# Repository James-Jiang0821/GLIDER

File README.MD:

# Glider System

Top-level repo for the underwater glider. 

ROS 2 stack on the Raspberry Pi, Teensy firmware for the P&R and VBD boards, KiCad designs for the custom electronics, and post-test analysis tooling.

Each subfolder has its own README with full details.

## Subsystems

- **[ROS2_SYSTEM/](ROS2_SYSTEM/README.md)** — ROS 2 Jazzy stack on the Raspberry Pi: sensor drivers, mission state machine, inner/outer-loop controller, safety watchdog, Iridium telemetry, and the CAN bridge to the Teensy boards.
- **[TEENSY/](TEENSY/)** — Teensy 4.0 firmware for the actuator boards.
  - **[tsyPR/](TEENSY/tsyPR/README.md)** — Pitch & Roll firmware (stepper-driven pitch mass + roll mass).
  - **[tsyVBDL/](TEENSY/tsyVBDL/README.md)** — Variable Buoyancy Device firmware (lead-screw piston with closed-loop position control).
- **[PCB/](PCB/README.MD)** — KiCad schematics and layouts for the custom P&R and VBD boards.
- **[BATTERY_BOARD/](BATTERY_BOARD/README.MD)** — KiCad designs for the P&R and VBD battery boards (A/B variants).
- **[ROS2_TESTING/](ROS2_TESTING/README.md)** — Post-test analysis scripts for ROS 2 bag files (`.mcap` to CSV).

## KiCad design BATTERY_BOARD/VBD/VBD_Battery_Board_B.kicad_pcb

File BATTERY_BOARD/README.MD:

# Battery Board

KiCad design files for the glider's battery boards.

## Subsystems

- **P&R/** — Pitch & Roll battery board. Powers the P&R subsystem; A and B variants.
- **VBD/** — Variable Buoyancy Device battery board. Powers the VBD subsystem; A and B variants.

Each folder contains the KiCad schematic (`.kicad_sch`), PCB layout (`.kicad_pcb`), and project file (`.kicad_pro`) for both A and B revisions.

## Authors

Bartol Vahcic

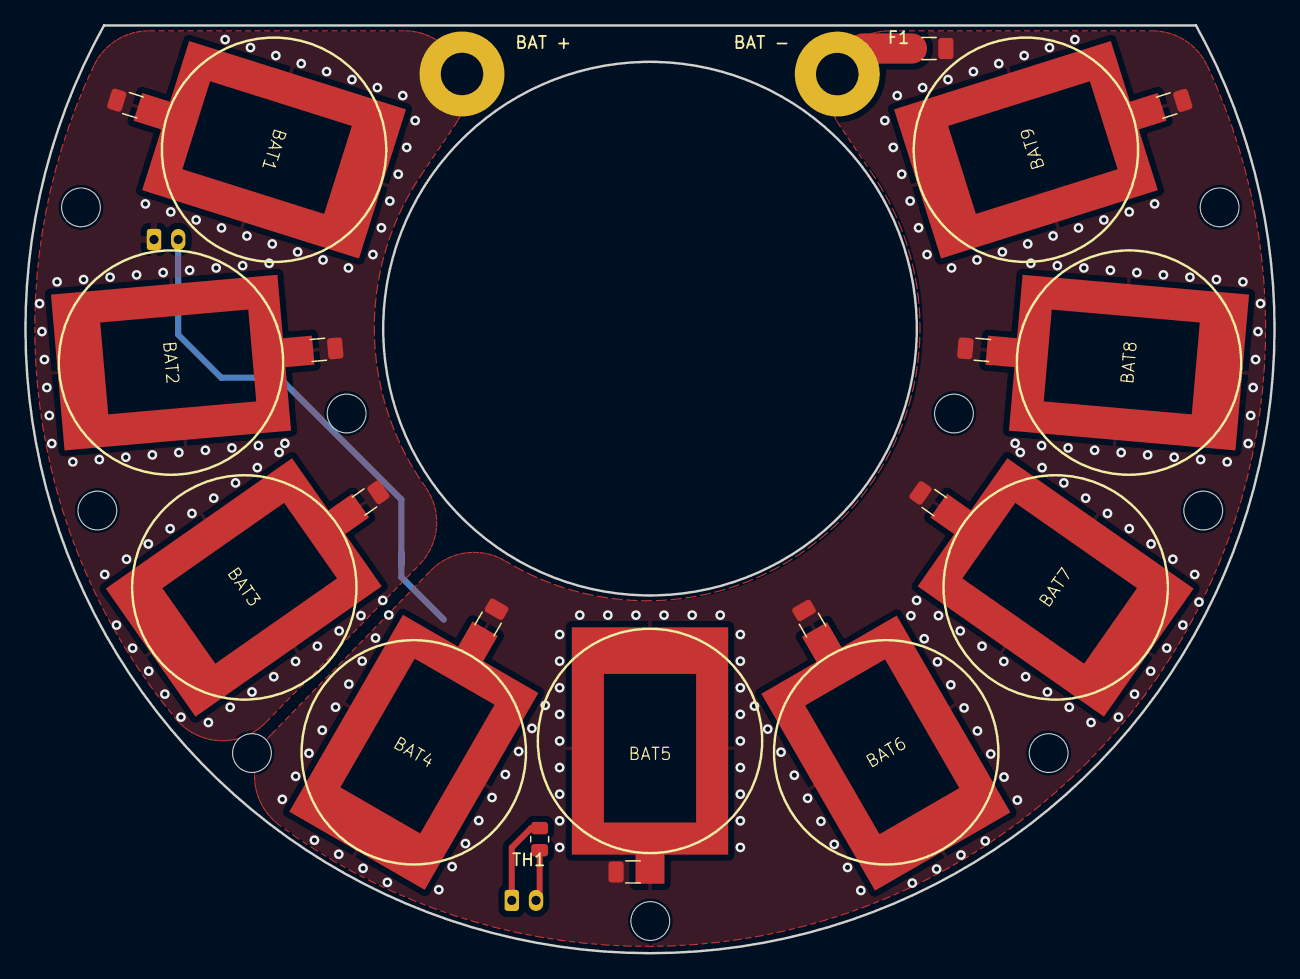
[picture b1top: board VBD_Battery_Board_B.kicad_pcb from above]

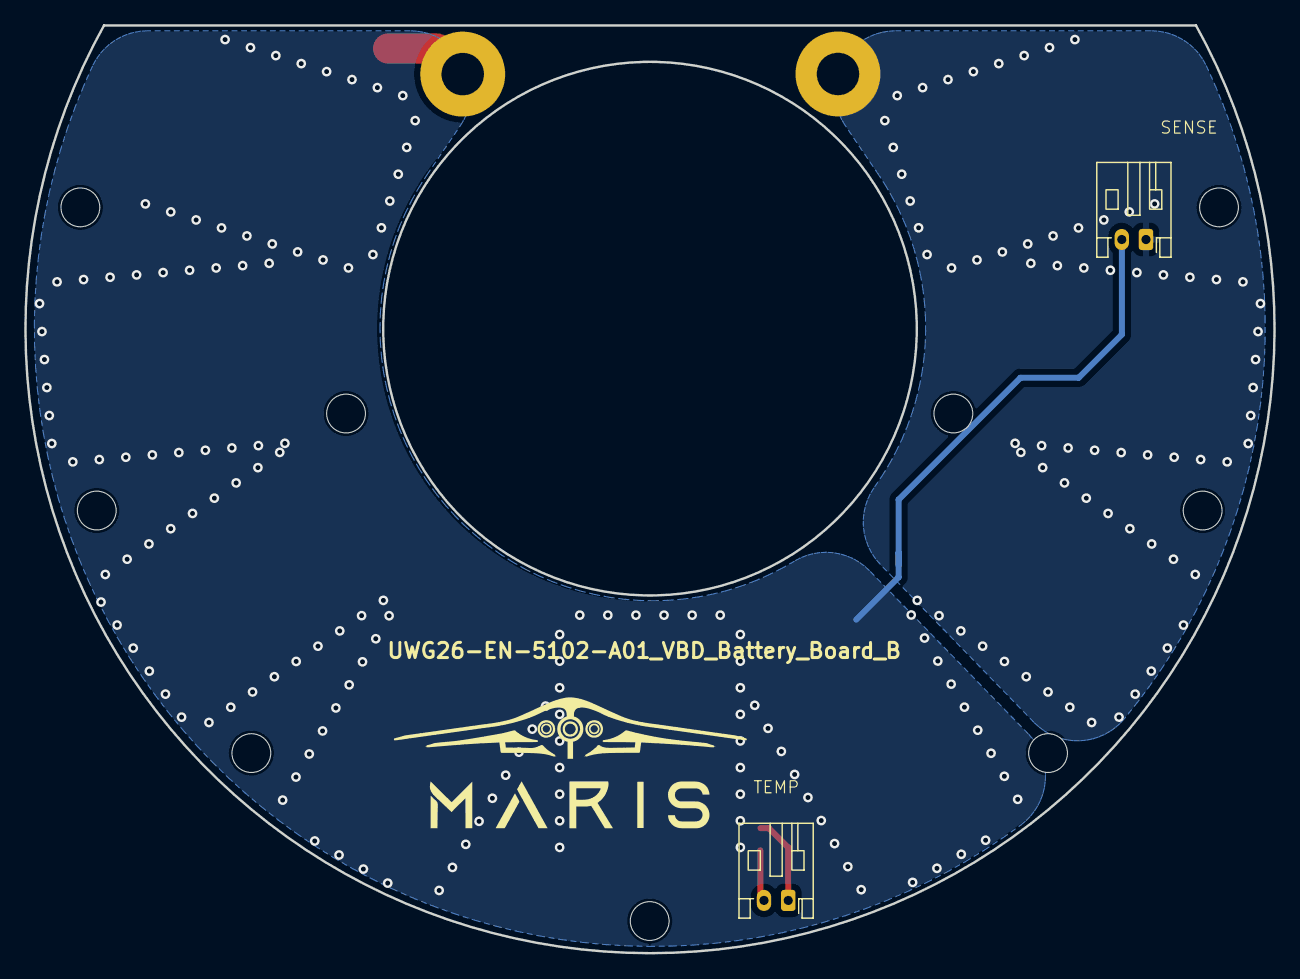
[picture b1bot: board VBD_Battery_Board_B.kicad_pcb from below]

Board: 2 copper layers, 103.0 x 76.5 mm, 15 parts (2 on the bottom side), 5 nets.

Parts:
BAT1, BAT2, BAT3, BAT4, BAT5, BAT6, BAT7, BAT8, BAT9: Keystone_109-2
BAT +: Conn_01x01_Pin; MountingHole_3.5mm_Pad
BAT -: Conn_01x01_Pin; MountingHole_3.5mm_Pad
F1: Fuse; Fuse_1206_3216Metric
J1, J4: Conn_01x02_Pin; JST_PH_S2B-PH-K_1x02_P2.00mm_Horizontal
TH1: Thermistor_NTC; R_0805_2012Metric

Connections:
/S1_POS: BAT1.1, BAT2.1, BAT3.1, BAT +.1, J1.1
/S3_POS: BAT4.1, BAT5.1, BAT6.1, BAT7.1, BAT8.1, BAT9.1, F1.2, J1.2
/TEMP: J4.1, TH1.1
/TEMP_GND: J4.2, TH1.2
unnamed: BAT -.1, F1.1

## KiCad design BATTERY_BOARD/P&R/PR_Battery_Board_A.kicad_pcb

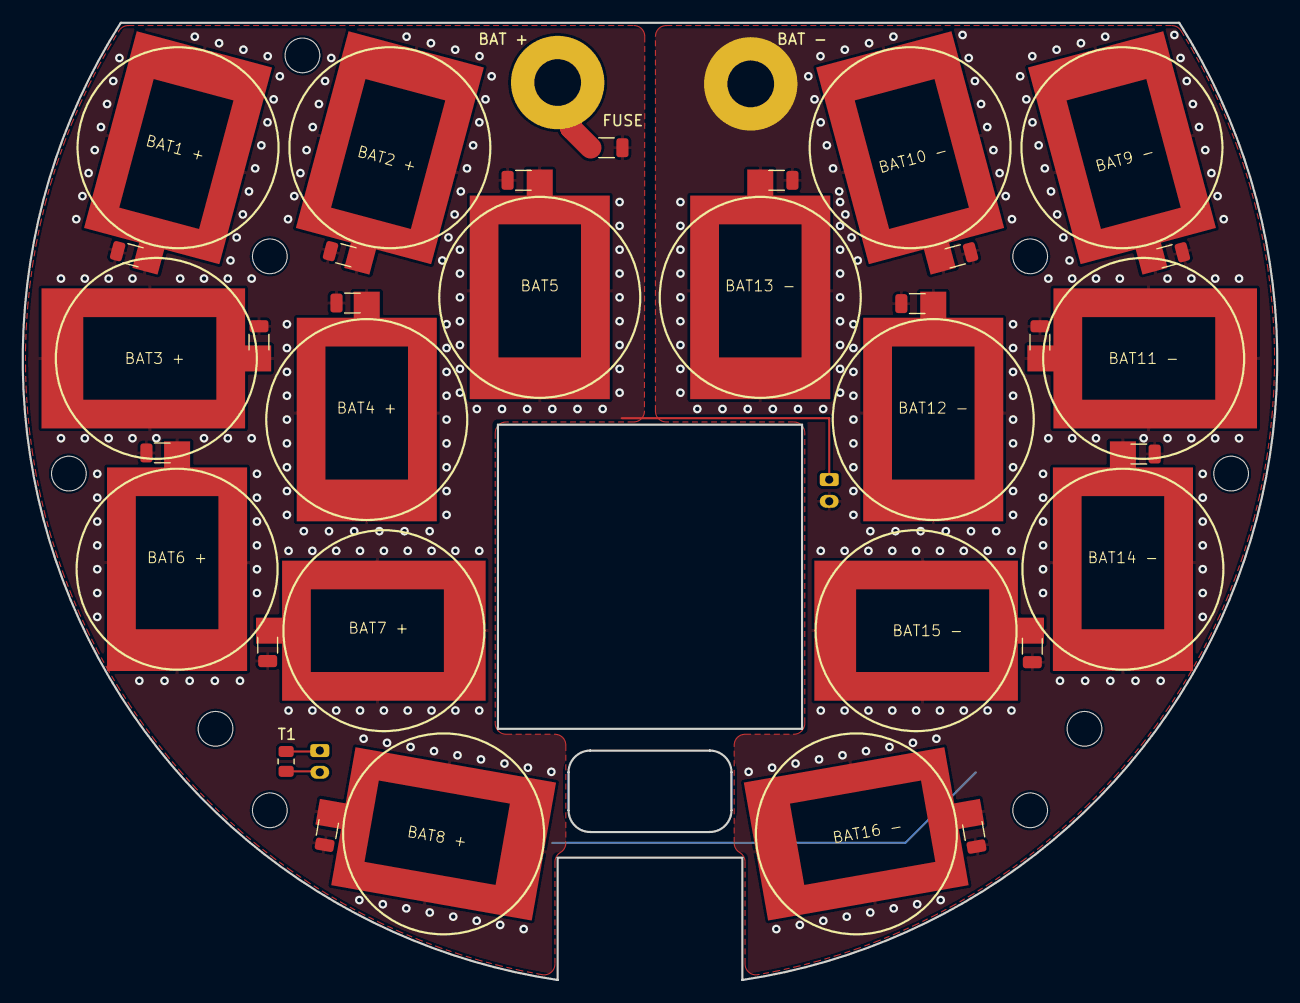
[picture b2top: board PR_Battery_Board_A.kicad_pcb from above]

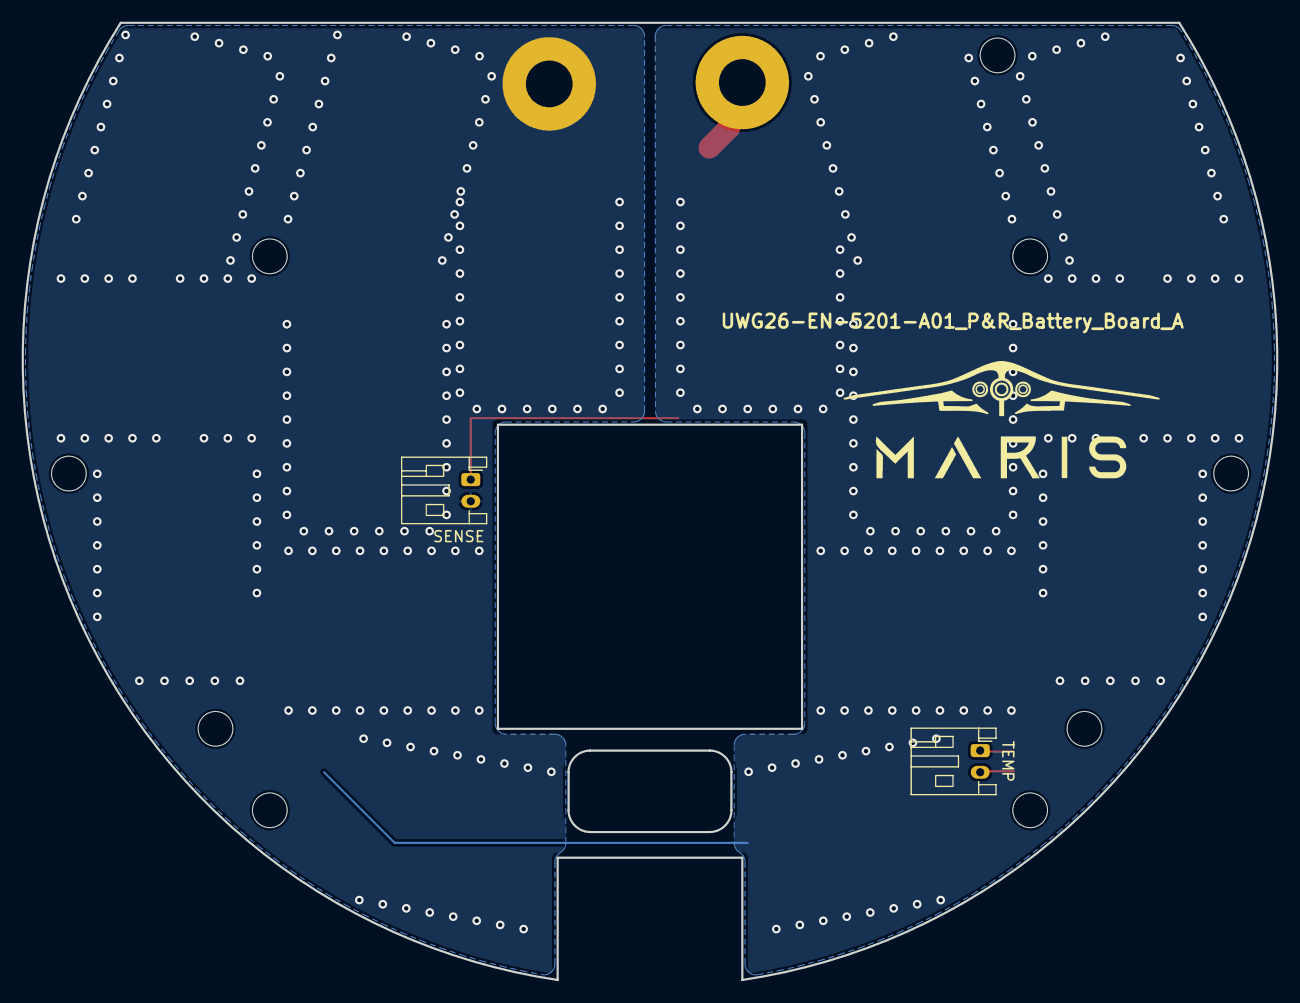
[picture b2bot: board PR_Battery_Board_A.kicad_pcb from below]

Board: 2 copper layers, 115.5 x 88.1 mm, 38 parts (2 on the bottom side), 5 nets.

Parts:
BAT1 +, BAT2 +, BAT3 +, BAT4 +, BAT5, BAT6 +, BAT7 +, BAT8 +, BAT9 -, BAT10 -, BAT11 -, BAT12 -, BAT13 -, BAT14 -, BAT15 -, BAT16 -: Keystone_109-2
BAT +: MountingHole_Pad; MountingHole_4.3mm_M4_Pad
BAT -: MountingHole_Pad; MountingHole_4.3mm_M4_Pad
F1, F2, F3, F4, F5, F6, F7, F8, F9, F10, F11, F12, F13, F14, F15, F16: DNP; R_1206_3216Metric
FUSE: F10; R_1206_3216Metric
SENSE: Conn_01x02_Pin; JST_PH_S2B-PH-K_1x02_P2.00mm_Horizontal
T1: 10K NTC; R_0805_2012Metric
TEMP: Conn_01x02_Pin; JST_PH_S2B-PH-K_1x02_P2.00mm_Horizontal

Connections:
/B_PLUS: BAT +.1, FUSE.2
/NTC_GND: T1.1, TEMP.2
/NTC_SIG: T1.2, TEMP.1
/S1_POS: BAT1 +.1, BAT2 +.1, BAT3 +.1, BAT4 +.1, BAT5.1, BAT6 +.1, BAT7 +.1, BAT8 +.1, F1.1, F1.2, F2.1, F2.2, F3.1, F3.2, F4.1, F4.2, F5.1, F5.2, F6.1, F6.2, F7.1, F7.2, F8.1, F8.2, FUSE.1, SENSE.1
/S2_NEG: BAT9 -.1, BAT10 -.1, BAT11 -.1, BAT12 -.1, BAT13 -.1, BAT14 -.1, BAT15 -.1, BAT16 -.1, BAT -.1, F9.1, F9.2, F10.1, F10.2, F11.1, F11.2, F12.1, F12.2, F13.1, F13.2, F14.1, F14.2, F15.1, F15.2, F16.1, F16.2, SENSE.2

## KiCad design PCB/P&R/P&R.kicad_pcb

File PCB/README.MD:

# PCB

KiCad design files for the glider's custom boards.

## Subsystems

- **P&R/** — Pitch & Roll board. Drives the pitch and roll actuators; also connects to the Raspberry Pi.
- **VBD/** — Variable Buoyancy Device board. Drives the VBD pump/valve subsystem.

Each folder contains the KiCad schematic (`.kicad_sch`) and PCB layout (`.kicad_pcb`); `P&R/` also includes the project file (`.kicad_pro`).

## Authors

Qihao Zhang

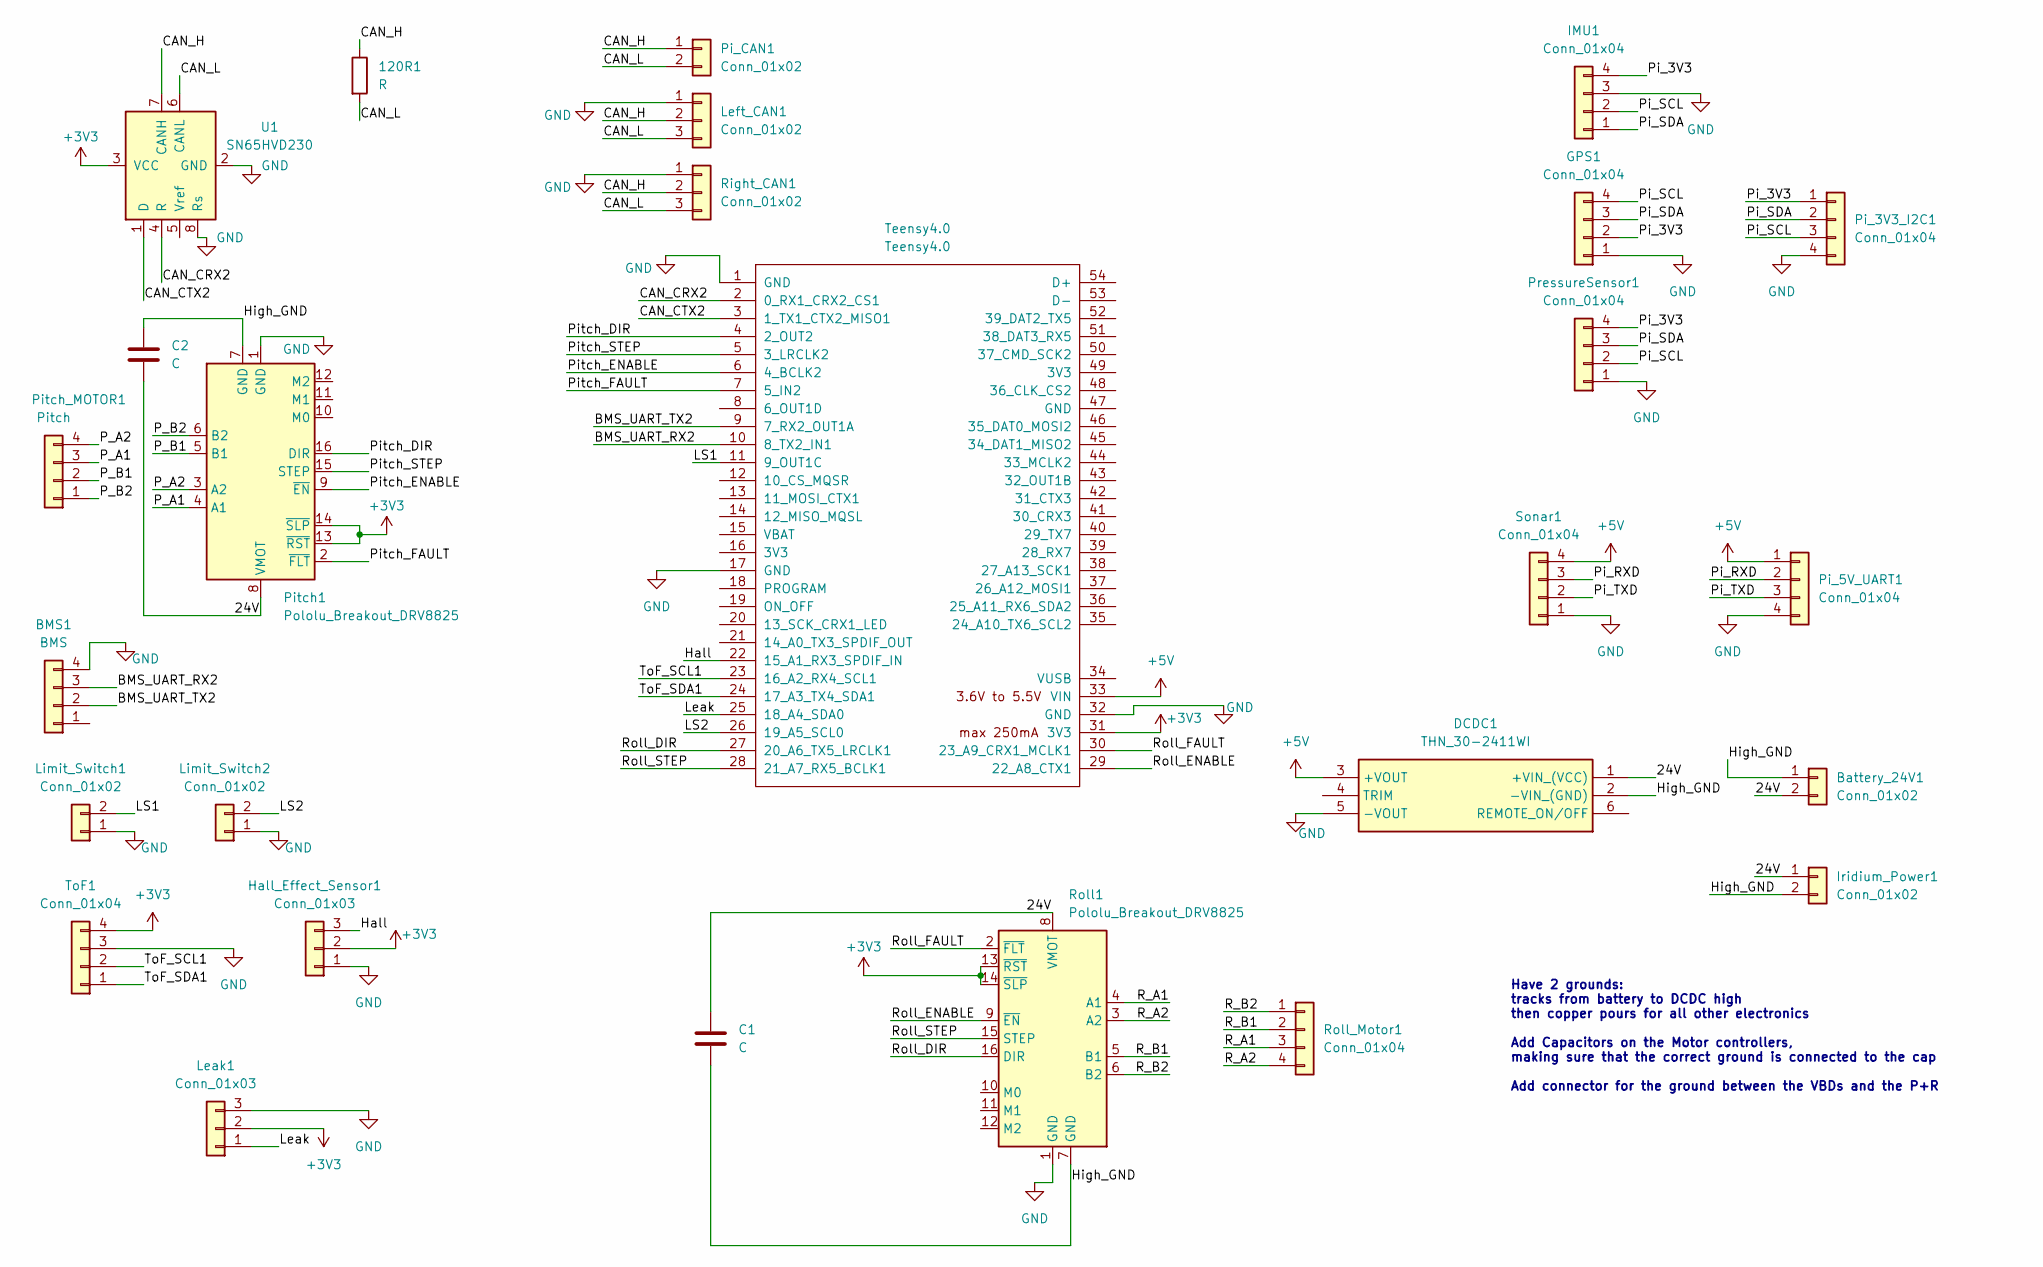
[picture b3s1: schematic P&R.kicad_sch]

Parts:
120R1: R; R_0805_2012Metric_Pad1.20x1.40mm_HandSolder
BMS1: BMS; JST_XH_B4B-XH-A_1x04_P2.50mm_Vertical
Battery_24V1: Conn_01x02; TerminalBlock_WAGO_2601-1102_1x02_P3.50mm_Horizontal
C1, C2: C; CP_Radial_D8.0mm_P3.50mm
DCDC1: THN_30-2411WI; THN302415WI; Mouser Part Number 495-THN-30-2411WI
GPS1: Conn_01x04; NewnewGNSS
Hall_Effect_Sensor1: Conn_01x03; JST_XH_B3B-XH-A_1x03_P2.50mm_Vertical
IMU1: Conn_01x04; JST_XH_B4B-XH-A_1x04_P2.50mm_Vertical
Iridium_Power1: Conn_01x02; JST_XH_B2B-XH-A_1x02_P2.50mm_Vertical
Leak1: Conn_01x03; SOS_Leak_Sensor_Board
Left_CAN1: Conn_01x02; JST_XH_B3B-XH-A_1x03_P2.50mm_Vertical
Limit_Switch1, Limit_Switch2: Conn_01x02; JST_XH_B2B-XH-A_1x02_P2.50mm_Vertical
Pi_3V3_I2C1, Pi_5V_UART1: Conn_01x04; JST_XH_B4B-XH-A_1x04_P2.50mm_Vertical
Pi_CAN1: Conn_01x02; JST_XH_B2B-XH-A_1x02_P2.50mm_Vertical
Pitch1: Pololu_Breakout_DRV8825; Pololu_Breakout-16_15.2x20.3mm
Pitch_MOTOR1: Pitch; JST_XH_B4B-XH-A_1x04_P2.50mm_Vertical
PressureSensor1: Conn_01x04; JST_XH_B4B-XH-A_1x04_P2.50mm_Vertical
Right_CAN1: Conn_01x02; JST_XH_B3B-XH-A_1x03_P2.50mm_Vertical
Roll1: Pololu_Breakout_DRV8825; Pololu_Breakout-16_15.2x20.3mm
Roll_Motor1: Conn_01x04; JST_XH_B4B-XH-A_1x04_P2.50mm_Vertical
Sonar1: Conn_01x04; JST_XH_B4B-XH-A_1x04_P2.50mm_Vertical
Teensy4.0: Teensy4.0; Teensy40
ToF1: Conn_01x04; JST_XH_B4B-XH-A_1x04_P2.50mm_Vertical
U1: SN65HVD230; SOIC-8_3.9x4.9mm_P1.27mm

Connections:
+3V3: Hall_Effect_Sensor1.2, Leak1.2, Pitch1.13 (~RST), Pitch1.14 (~SLP), Roll1.13 (~RST), Roll1.14 (~SLP), Teensy4.0.31 (3V3), ToF1.4, U1.3 (VCC)
+5V: DCDC1.3 (+VOUT), Pi_5V_UART1.1, Sonar1.4, Teensy4.0.33 (VIN)
/24V: Battery_24V1.2, C1.1, C2.2, DCDC1.1 (+VIN_(VCC)), Iridium_Power1.1, Pitch1.8 (VMOT), Roll1.8 (VMOT)
/BMS_UART_RX2: BMS1.3, Teensy4.0.10 (8_TX2_IN1)
/BMS_UART_TX2: BMS1.2, Teensy4.0.9 (7_RX2_OUT1A)
/CAN_CRX2: Teensy4.0.2 (0_RX1_CRX2_CS1), U1.4 (R)
/CAN_CTX2: Teensy4.0.3 (1_TX1_CTX2_MISO1), U1.1 (D)
/CAN_H: 120R1.1, Left_CAN1.2, Pi_CAN1.1, Right_CAN1.2, U1.7 (CANH)
/CAN_L: 120R1.2, Left_CAN1.3, Pi_CAN1.2, Right_CAN1.3, U1.6 (CANL)
/Hall: Hall_Effect_Sensor1.3, Teensy4.0.22 (15_A1_RX3_SPDIF_IN)
/High_GND: Battery_24V1.1, C1.2, C2.1, DCDC1.2 (-VIN_(GND)), Iridium_Power1.2, Pitch1.7 (GND), Roll1.7 (GND)
/LS1: Limit_Switch1.2, Teensy4.0.11 (9_OUT1C)
/LS2: Limit_Switch2.2, Teensy4.0.26 (19_A5_SCL0)
/Leak: Leak1.1, Teensy4.0.25 (18_A4_SDA0)
/P_A1: Pitch1.4 (A1), Pitch_MOTOR1.3
/P_A2: Pitch1.3 (A2), Pitch_MOTOR1.4
/P_B1: Pitch1.5 (B1), Pitch_MOTOR1.2
/P_B2: Pitch1.6 (B2), Pitch_MOTOR1.1
/Pi_3V3: GPS1.2, IMU1.4, Pi_3V3_I2C1.1, PressureSensor1.4
/Pi_RXD: Pi_5V_UART1.2, Sonar1.3
/Pi_SCL: GPS1.4, IMU1.2, Pi_3V3_I2C1.3, PressureSensor1.2
/Pi_SDA: GPS1.3, IMU1.1, Pi_3V3_I2C1.2, PressureSensor1.3
/Pi_TXD: Pi_5V_UART1.3, Sonar1.2
/Pitch_DIR: Pitch1.16 (DIR), Teensy4.0.4 (2_OUT2)
/Pitch_ENABLE: Pitch1.9 (~EN), Teensy4.0.6 (4_BCLK2)
/Pitch_FAULT: Pitch1.2 (~FLT), Teensy4.0.7 (5_IN2)
/Pitch_STEP: Pitch1.15 (STEP), Teensy4.0.5 (3_LRCLK2)
/R_A1: Roll1.4 (A1), Roll_Motor1.3
/R_A2: Roll1.3 (A2), Roll_Motor1.4
/R_B1: Roll1.5 (B1), Roll_Motor1.2
/R_B2: Roll1.6 (B2), Roll_Motor1.1
/Roll_DIR: Roll1.16 (DIR), Teensy4.0.27 (20_A6_TX5_LRCLK1)
/Roll_ENABLE: Roll1.9 (~EN), Teensy4.0.29 (22_A8_CTX1)
/Roll_FAULT: Roll1.2 (~FLT), Teensy4.0.30 (23_A9_CRX1_MCLK1)
/Roll_STEP: Roll1.15 (STEP), Teensy4.0.28 (21_A7_RX5_BCLK1)
/ToF_SCL1: Teensy4.0.23 (16_A2_RX4_SCL1), ToF1.2
/ToF_SDA1: Teensy4.0.24 (17_A3_TX4_SDA1), ToF1.1
GND: BMS1.4, DCDC1.5 (-VOUT), GPS1.1, Hall_Effect_Sensor1.1, IMU1.3, Leak1.3, Left_CAN1.1, Limit_Switch1.1, Limit_Switch2.1, Pi_3V3_I2C1.4, Pi_5V_UART1.4, Pitch1.1 (GND), PressureSensor1.1, Right_CAN1.1, Roll1.1 (GND), Sonar1.1, Teensy4.0.1 (GND), Teensy4.0.17 (GND), Teensy4.0.32 (GND), ToF1.3, U1.2 (GND), U1.8 (Rs)

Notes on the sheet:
Have 2 grounds: tracks from battery to DCDC high then copper pours for all other electronics Add Capacitors on the Motor controllers, making sure that the correct ground is connected to the cap Add connector for the ground between the VBDs and the P+R

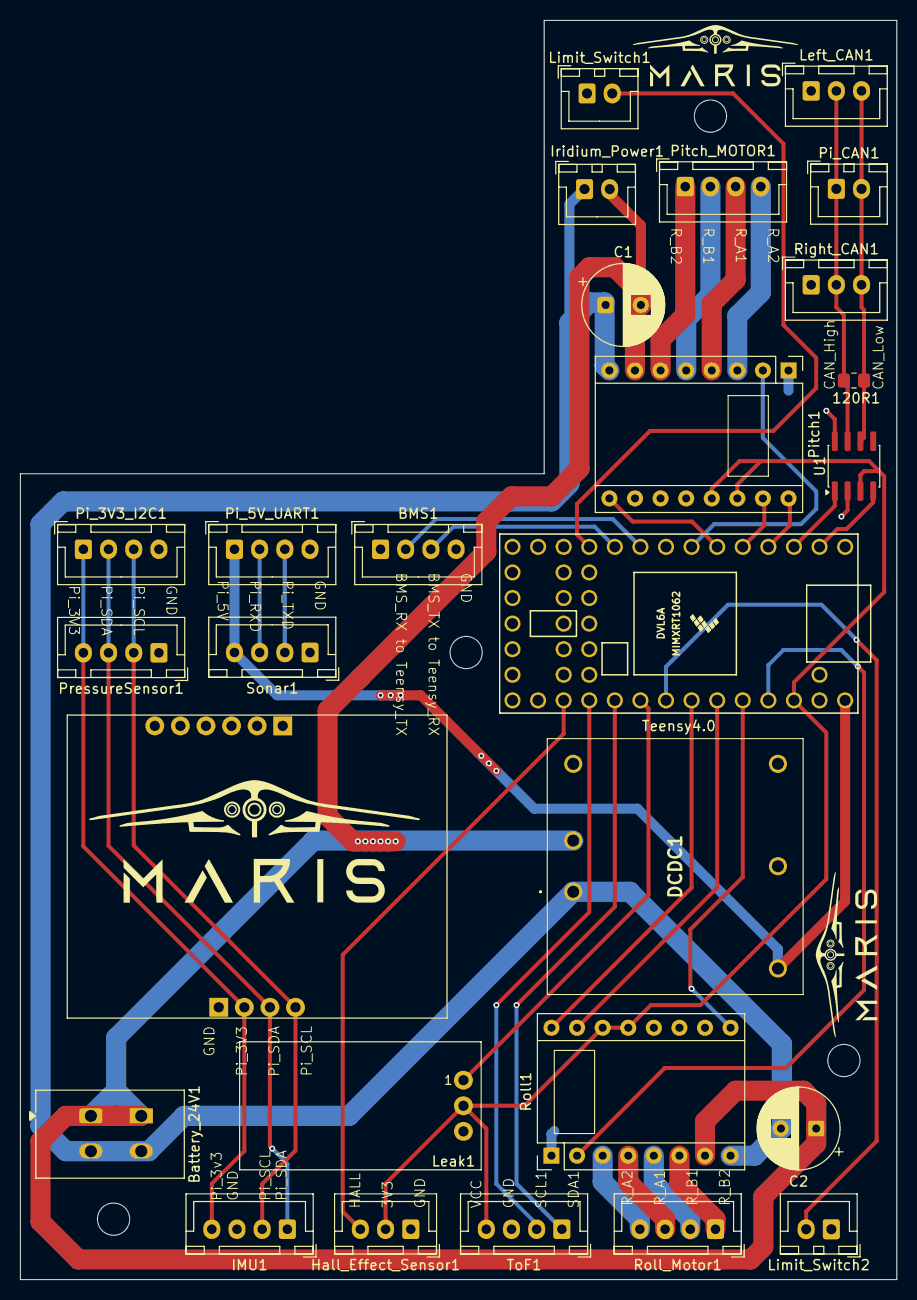
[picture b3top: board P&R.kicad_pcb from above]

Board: 2 copper layers, 87.0 x 125.0 mm, 27 parts (0 on the bottom side), 38 nets.

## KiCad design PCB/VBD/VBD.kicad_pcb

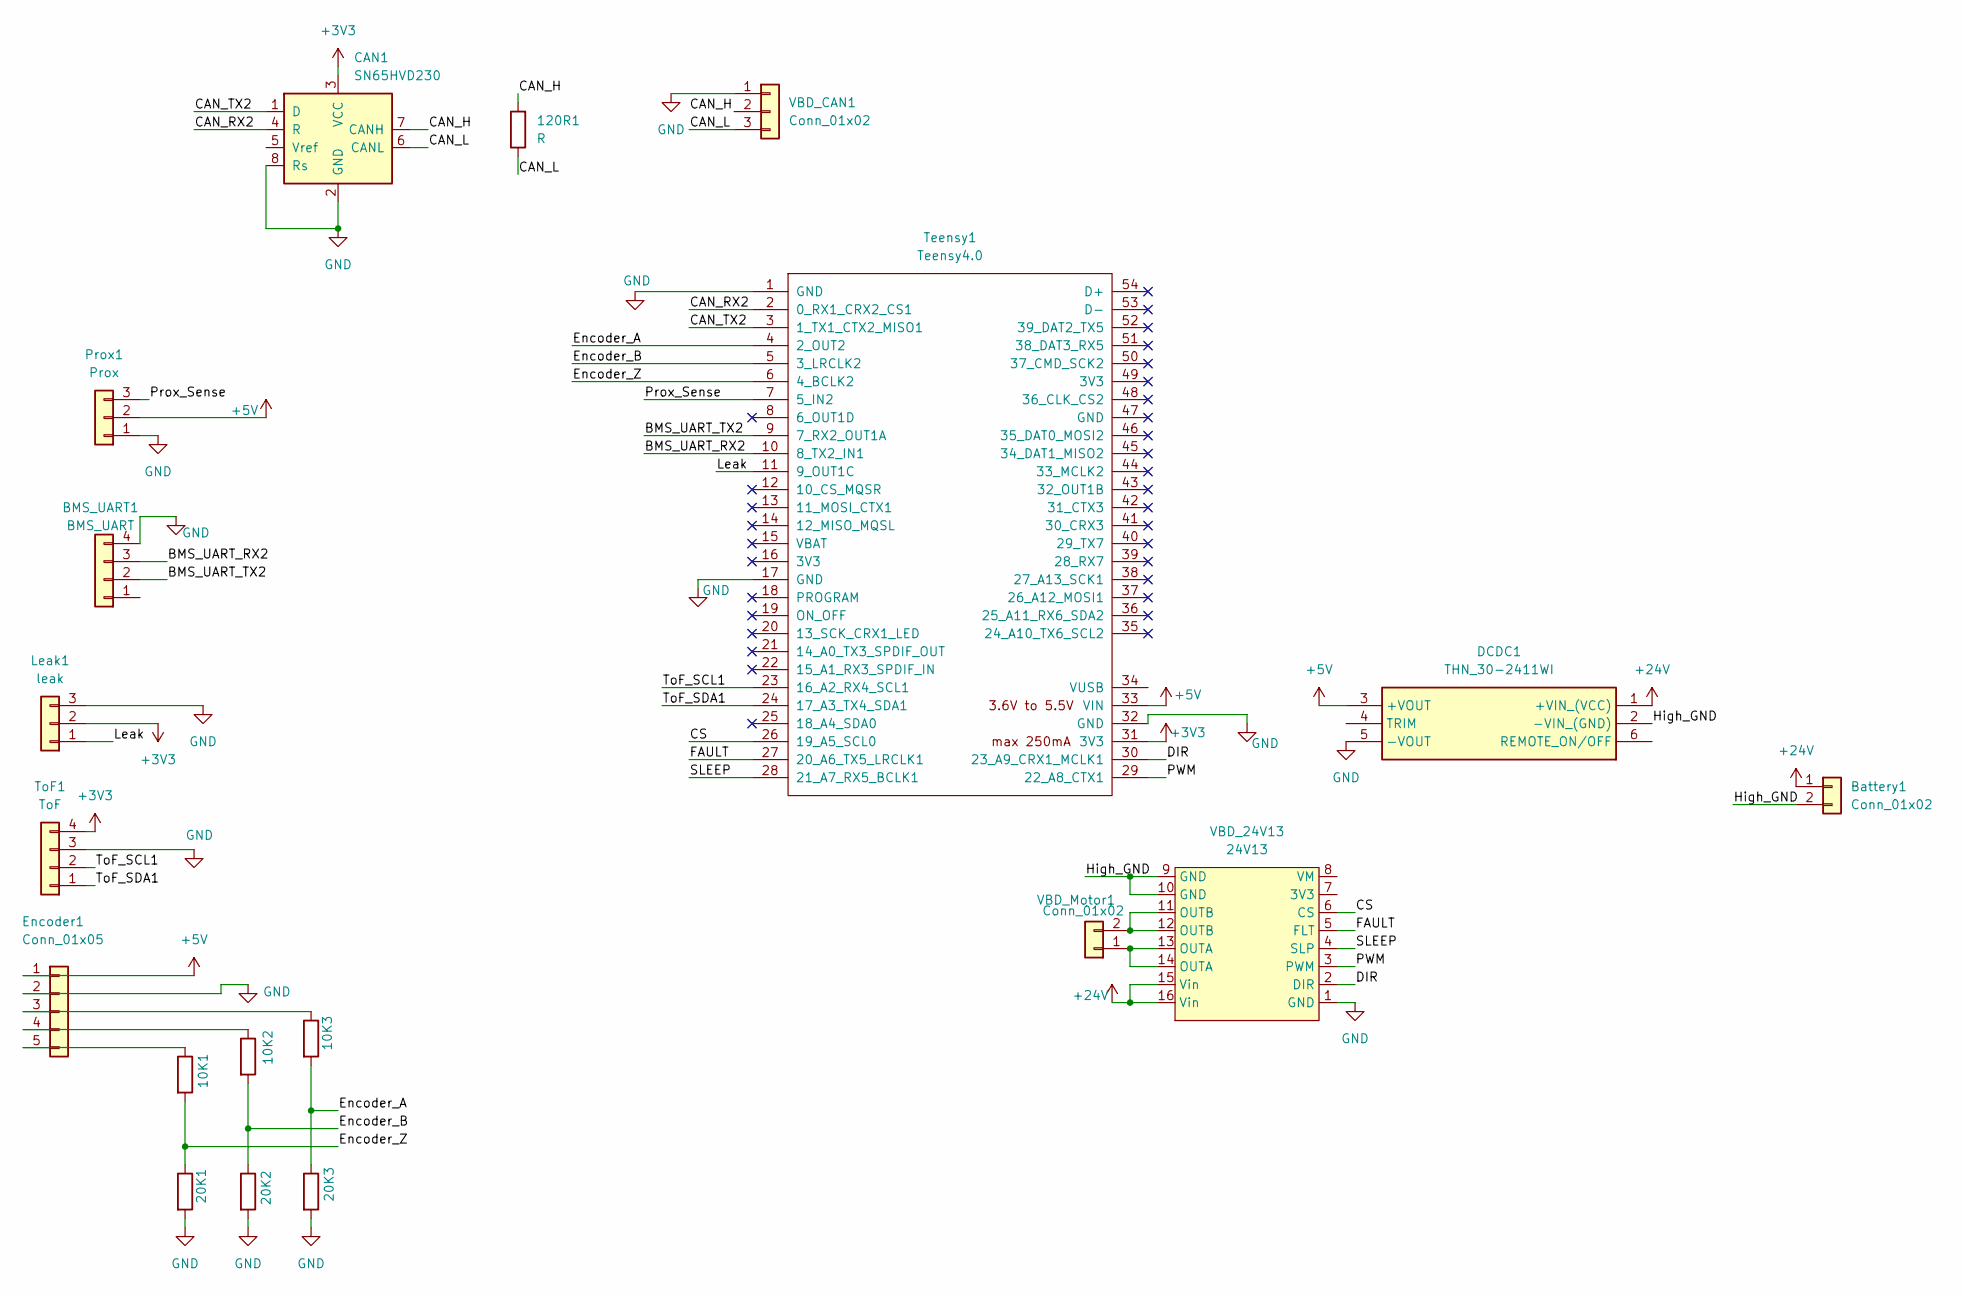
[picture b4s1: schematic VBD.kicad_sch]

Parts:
10K1, 10K2, 10K3, 20K1, 20K2, 20K3, 120R1: R; R_0805_2012Metric_Pad1.20x1.40mm_HandSolder
BMS_UART1: BMS_UART; JST_XH_B4B-XH-A_1x04_P2.50mm_Vertical
Battery1: Conn_01x02; TerminalBlock_WAGO_2601-1102_1x02_P3.50mm_Horizontal
CAN1: SN65HVD230; SOIC-8_3.9x4.9mm_P1.27mm
DCDC1: THN_30-2411WI; THN302415WI; Mouser Part Number 495-THN-30-2411WI
Encoder1: Conn_01x05; JST_XH_B5B-XH-A_1x05_P2.50mm_Vertical
Leak1: leak; SOS_Leak_Sensor_Board
Prox1: Prox; JST_XH_B3B-XH-A_1x03_P2.50mm_Vertical
Teensy1: Teensy4.0; Teensy40
ToF1: ToF; JST_XH_B4B-XH-A_1x04_P2.50mm_Vertical
VBD_24V13: 24V13; new24V13
VBD_CAN1: Conn_01x02; JST_XH_B3B-XH-A_1x03_P2.50mm_Vertical
VBD_Motor1: Conn_01x02; JST_XH_B2B-XH-A_1x02_P2.50mm_Vertical

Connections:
+3V3: CAN1.3 (VCC), Leak1.2, Teensy1.31 (3V3), ToF1.4
+5V: DCDC1.3 (+VOUT), Encoder1.1, Prox1.2, Teensy1.33 (VIN)
+24V: Battery1.1, DCDC1.1 (+VIN_(VCC)), VBD_24V13.15 (Vin), VBD_24V13.16 (Vin)
/BMS_UART_RX2: BMS_UART1.3, Teensy1.10 (8_TX2_IN1)
/BMS_UART_TX2: BMS_UART1.2, Teensy1.9 (7_RX2_OUT1A)
/CAN_H: 120R1.2, CAN1.7 (CANH), VBD_CAN1.2
/CAN_L: 120R1.1, CAN1.6 (CANL), VBD_CAN1.3
/CAN_RX2: CAN1.4 (R), Teensy1.2 (0_RX1_CRX2_CS1)
/CAN_TX2: CAN1.1 (D), Teensy1.3 (1_TX1_CTX2_MISO1)
/CS: Teensy1.26 (19_A5_SCL0), VBD_24V13.6 (CS)
/DIR: Teensy1.30 (23_A9_CRX1_MCLK1), VBD_24V13.2 (DIR)
/Encoder_A: 10K3.2, 20K3.1, Teensy1.4 (2_OUT2)
/Encoder_B: 10K2.2, 20K2.1, Teensy1.5 (3_LRCLK2)
/Encoder_Z: 10K1.2, 20K1.1, Teensy1.6 (4_BCLK2)
/FAULT: Teensy1.27 (20_A6_TX5_LRCLK1), VBD_24V13.5 (FLT)
/High_GND: Battery1.2, DCDC1.2 (-VIN_(GND)), VBD_24V13.9 (GND), VBD_24V13.10 (GND)
/Leak: Leak1.1, Teensy1.11 (9_OUT1C)
/PWM: Teensy1.29 (22_A8_CTX1), VBD_24V13.3 (PWM)
/Prox_Sense: Prox1.3, Teensy1.7 (5_IN2)
/SLEEP: Teensy1.28 (21_A7_RX5_BCLK1), VBD_24V13.4 (SLP)
/ToF_SCL1: Teensy1.23 (16_A2_RX4_SCL1), ToF1.2
/ToF_SDA1: Teensy1.24 (17_A3_TX4_SDA1), ToF1.1
GND: 20K1.2, 20K2.2, 20K3.2, BMS_UART1.4, CAN1.2 (GND), CAN1.8 (Rs), DCDC1.5 (-VOUT), Encoder1.2, Leak1.3, Prox1.1, Teensy1.1 (GND), Teensy1.17 (GND), Teensy1.32 (GND), ToF1.3, VBD_24V13.1 (GND), VBD_CAN1.1
unnamed: 10K3.1, Encoder1.3
unnamed: 10K2.1, Encoder1.4
unnamed: 10K1.1, Encoder1.5
unnamed: VBD_24V13.13 (OUTA), VBD_24V13.14 (OUTA), VBD_Motor1.1
unnamed: VBD_24V13.11 (OUTB), VBD_24V13.12 (OUTB), VBD_Motor1.2

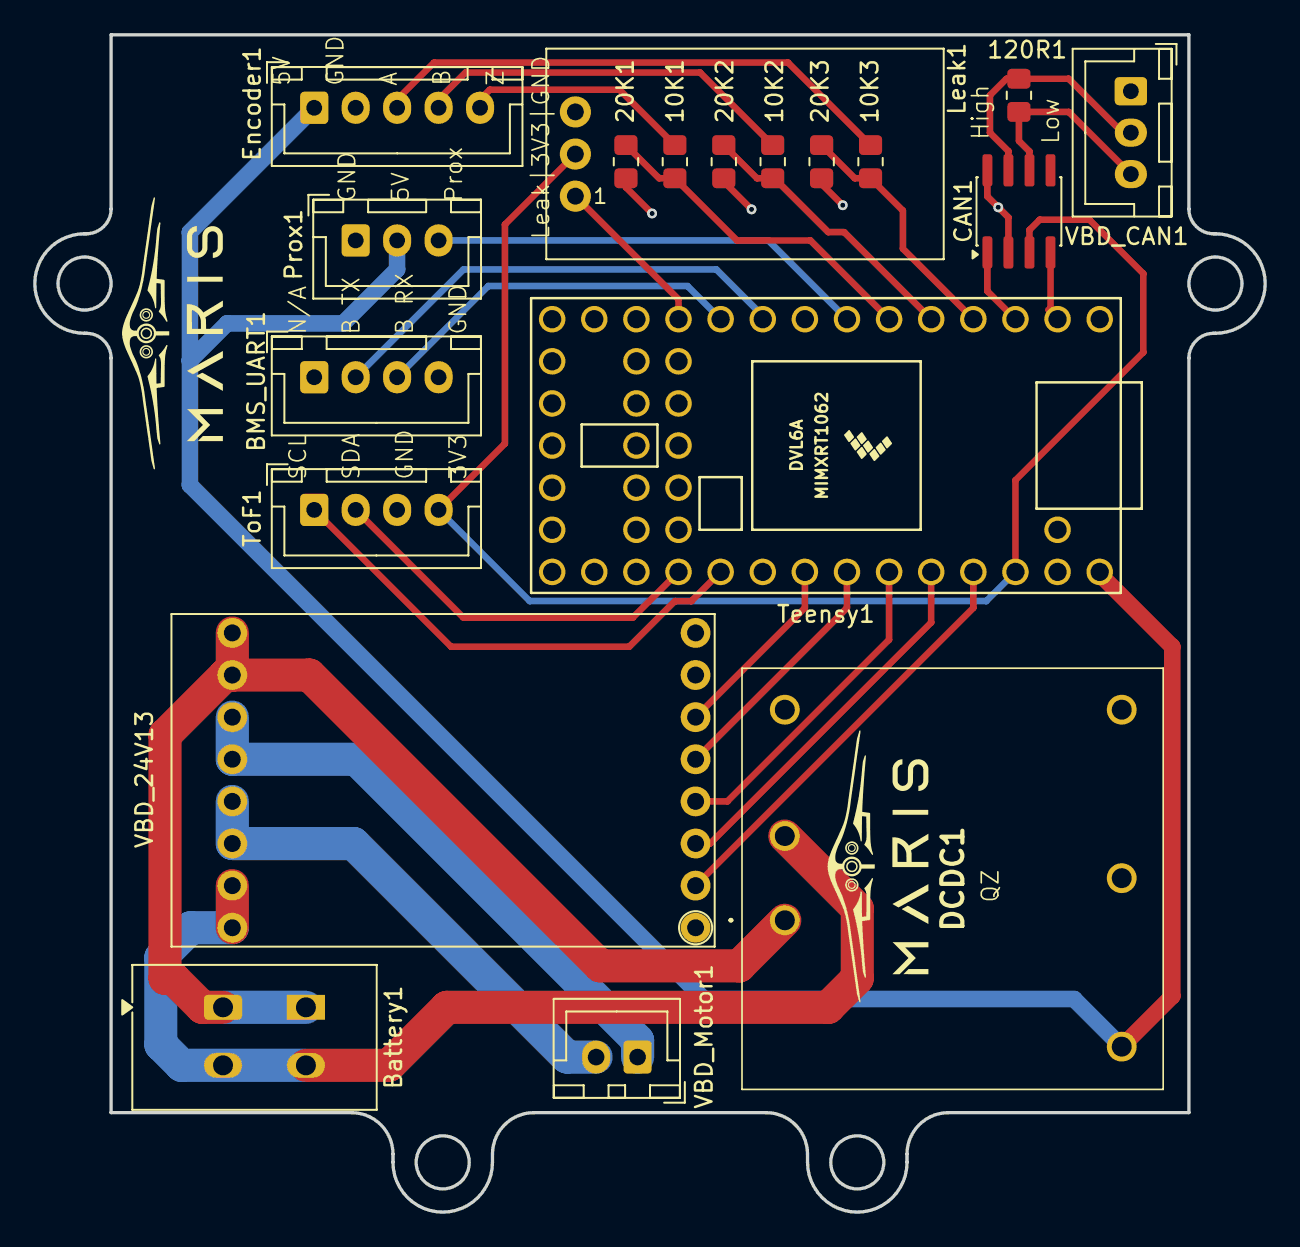
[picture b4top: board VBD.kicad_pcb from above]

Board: 2 copper layers, 74.2 x 71.0 mm, 19 parts (0 on the bottom side), 28 nets.

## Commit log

2026-04-26 version 1
2026-04-26 reorganise into ROS2_SYSTEM folder
2026-04-26 add ROS2_ANALYSIS folder
2026-04-26 added teensy code
2026-04-28 imu from v5 to v6
2026-04-30 pressure sensor calibration
2026-04-30 -bridge node less spammy if failed -bus state included
2026-05-01 new controller + mission + IMU changes
2026-05-01 CAN Unit Change
2026-05-02 pressure reconnect if fails
2026-05-02 added pressure fluid dnesity to glider parameters
2026-05-03 IMU calibration updates ( gyro + offset P&R)
2026-05-03 byte/bit coherence : CAN
2026-05-04 bridge node checks
2026-05-04 test for controller node added including a snapshot analysis to see reaction
2026-05-04 -removed uneeded nodes for tank test -glider params now homes all 3 subsystems
2026-05-06 new control updates - toggle + alpha
2026-05-07 -added pcb folder -added more readme comments
2026-05-07 -added battery board subfolder -added README for Teensy P&R
2026-05-07 main README commented
2026-05-07 folder ROS2 ANALYSIS changed to ROS2 TESTING
2026-05-11 glider param change
2026-05-11 bridge node
2026-05-11 updated teensy VBD code
2026-05-12 added pos% for tank test
2026-05-14 added tank test
2026-05-14 dead reckoning node
2026-05-15 imu changes
2026-05-15 added a position visualise node for Foxglove UI
2026-05-15 testing changes
2026-05-16 auto reconnect added for iridium & gnss
2026-05-16 pressure noise cancelation using EMA
2026-05-16 added glider.stl for 3d visualiser to have actual glider
2026-05-16 stl too big
2026-05-16 stl right size (16mb)
